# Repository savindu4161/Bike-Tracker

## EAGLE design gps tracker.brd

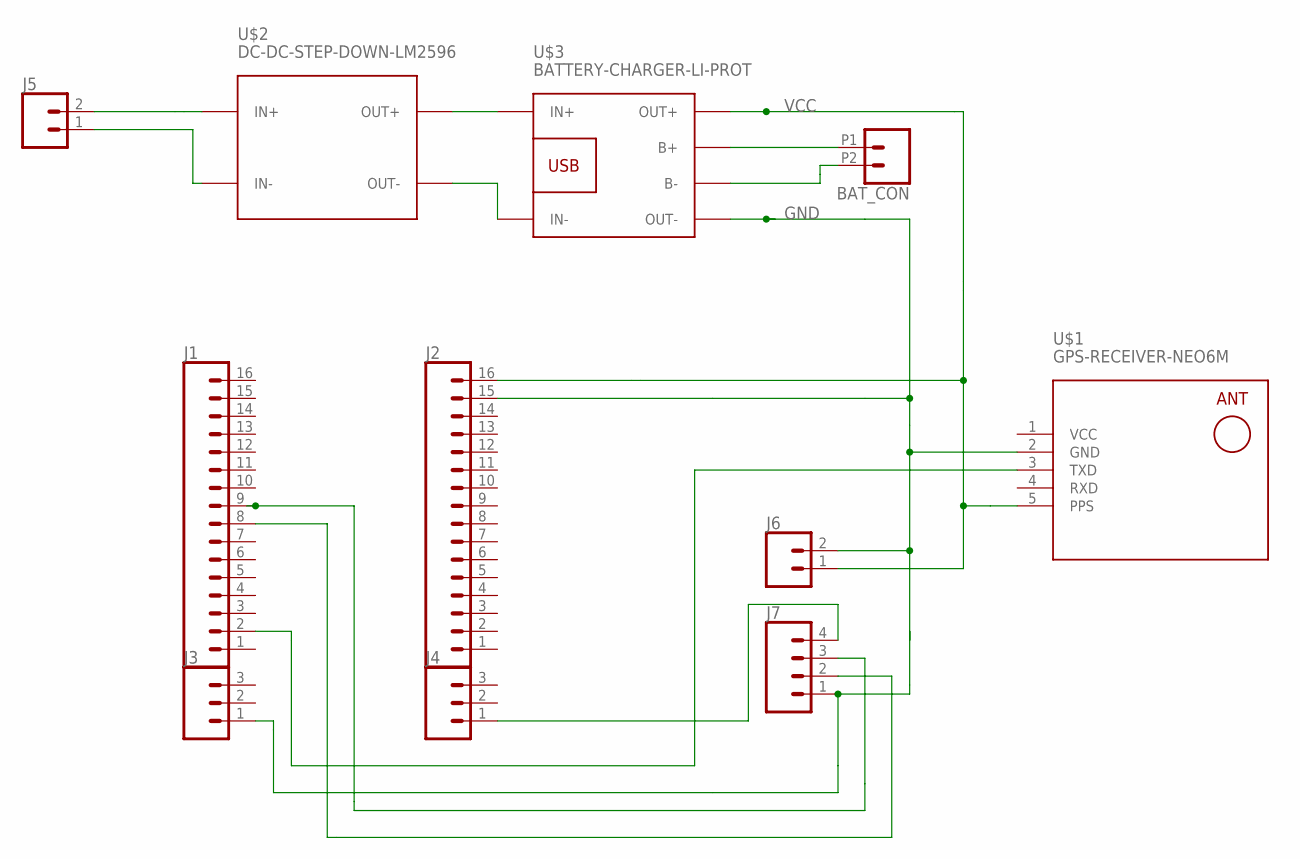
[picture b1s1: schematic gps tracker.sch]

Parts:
BAT_CON: CONN_022.54MM_SCREWTERM; 1X02_2.54_SCREWTERM
J1, J2: CONN_16LONGPADS; 1X16_LONGPADS
J3, J4: CONN_03LONGPADS; 1X03_LONGPADS
J5: CONN_025MM; SCREWTERMINAL-5MM-2
J6: CONN_02PTH3; 1X02_LONGPADS
J7: CONN_04LONGPADS; 1X04_LONGPADS
U$1: GPS-RECEIVER-NEO6M
U$2: DC-DC-STEP-DOWN-LM2596
U$3: BATTERY-CHARGER-LI-PROT

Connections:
GND: J2.15, J3.1, J6.2, J7.1, U$1.2 (GND), U$3.OUT-
unnamed: J5.2, U$2.IN+
unnamed: J5.1, U$2.IN-
unnamed: U$2.OUT+, U$3.IN+
unnamed: U$2.OUT-, U$3.IN-
unnamed: BAT_CON.P1 (1), U$3.B+
unnamed: BAT_CON.P2 (2), U$3.B-
unnamed: J4.1, J7.4
unnamed: J1.8, J7.2
unnamed: J1.9, J7.3
unnamed: J1.2, U$1.3 (TXD)
RXD: U$1.4 (RXD)
VCC: J2.16, J6.1, U$1.5 (PPS), U$3.OUT+

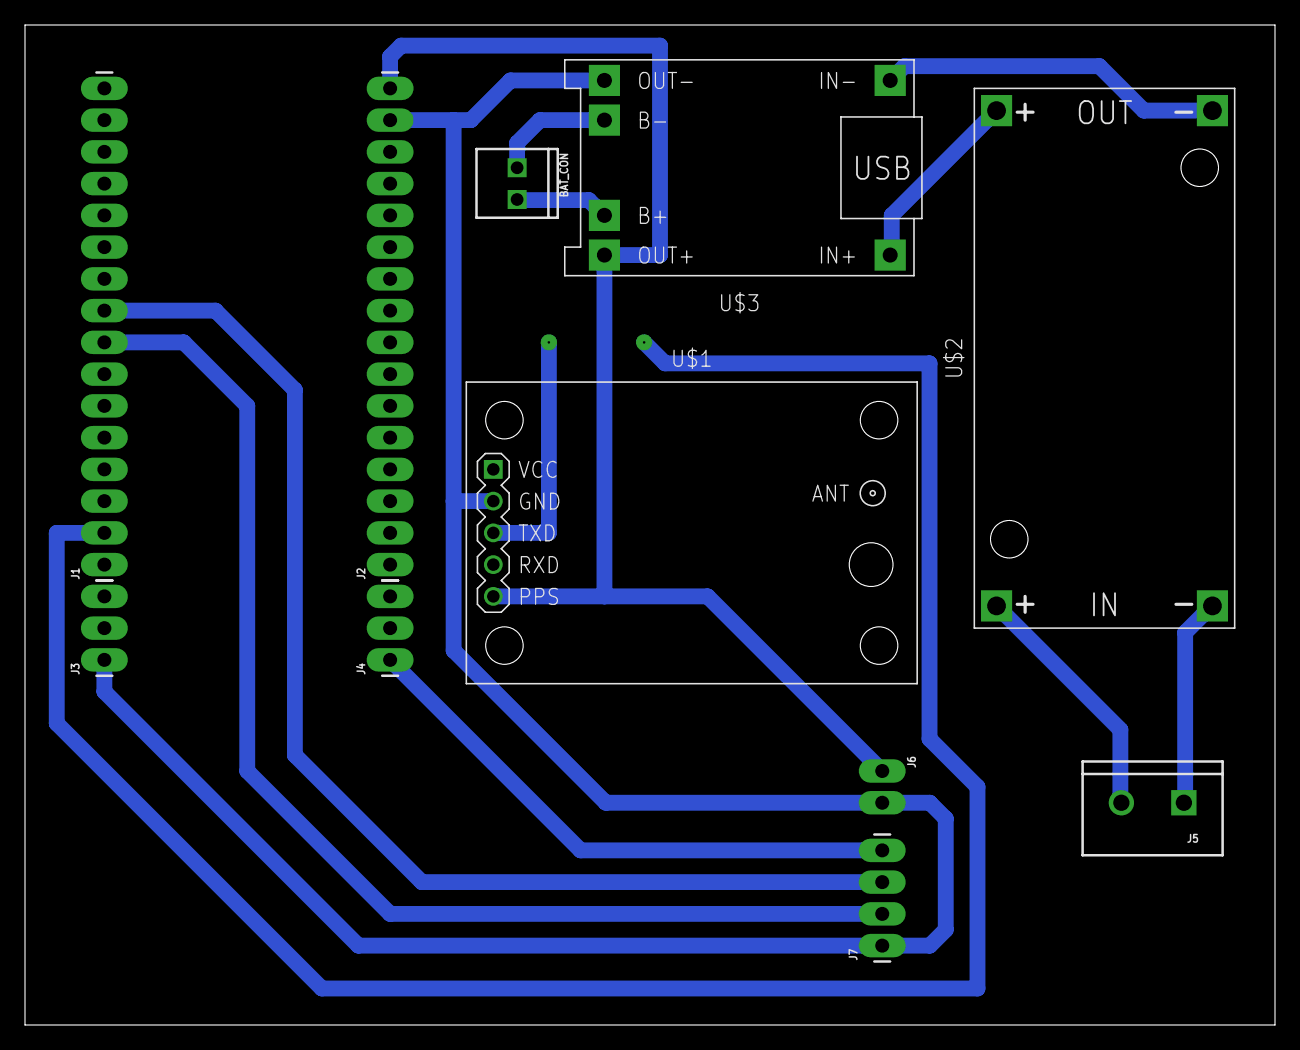
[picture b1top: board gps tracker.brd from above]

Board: 2 copper layers, 100.0 x 80.0 mm, 11 parts (0 on the bottom side), 12 nets.

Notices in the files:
parts and their libraries:
SparkFun-Connectors: Licensing: Creative Commons ShareAlike 4.0 International - https://creativecommons.org/licenses/by-sa/4.0
diy-modules: Released under the Creative Commons Attribution 4.0 International License: http://creativecommons.org/licenses/by/4.0
